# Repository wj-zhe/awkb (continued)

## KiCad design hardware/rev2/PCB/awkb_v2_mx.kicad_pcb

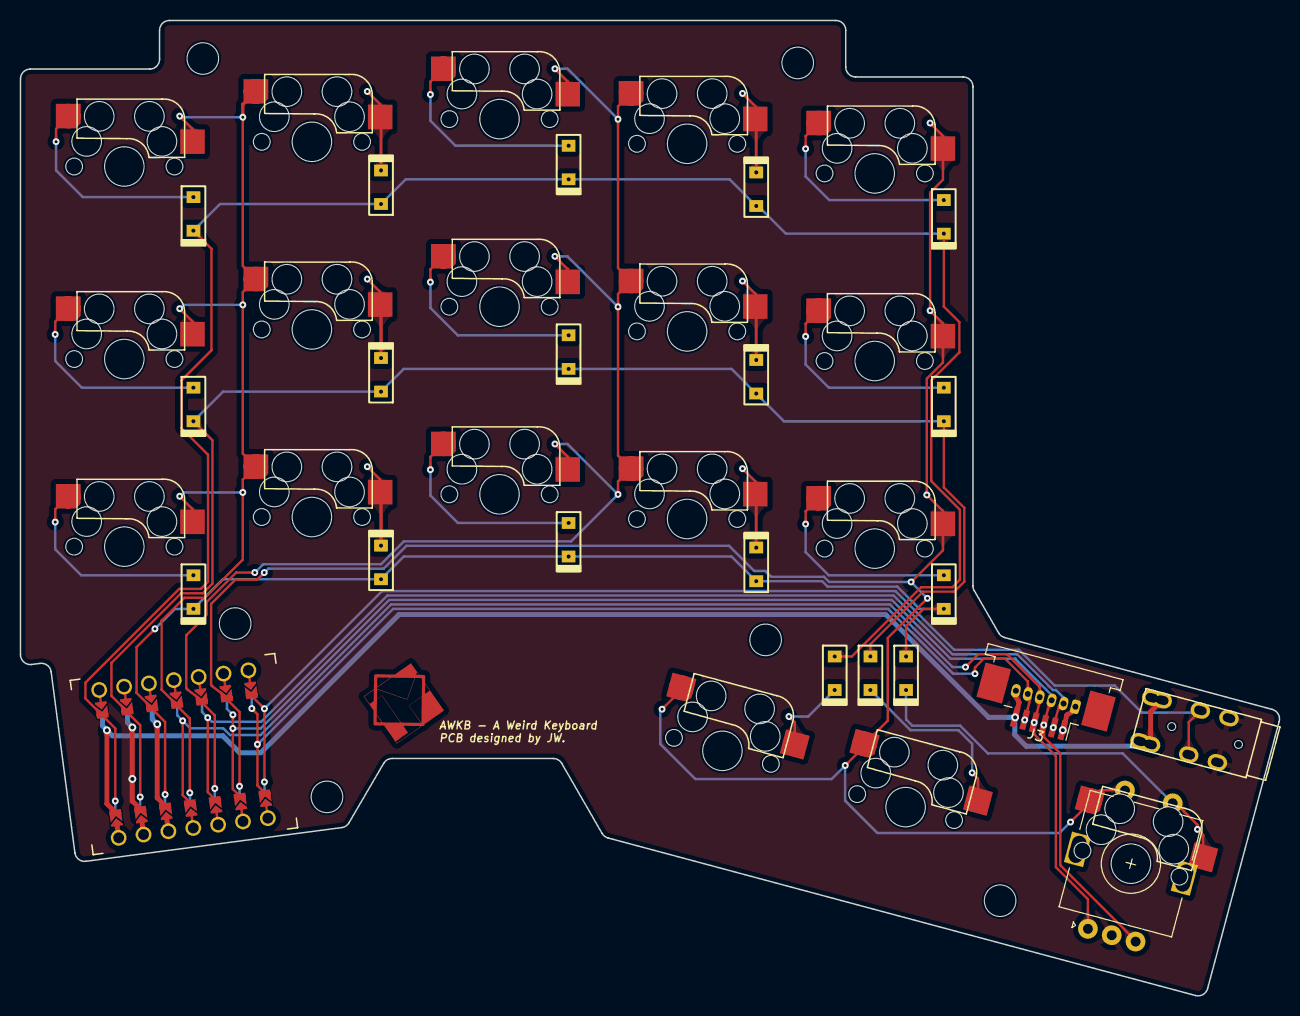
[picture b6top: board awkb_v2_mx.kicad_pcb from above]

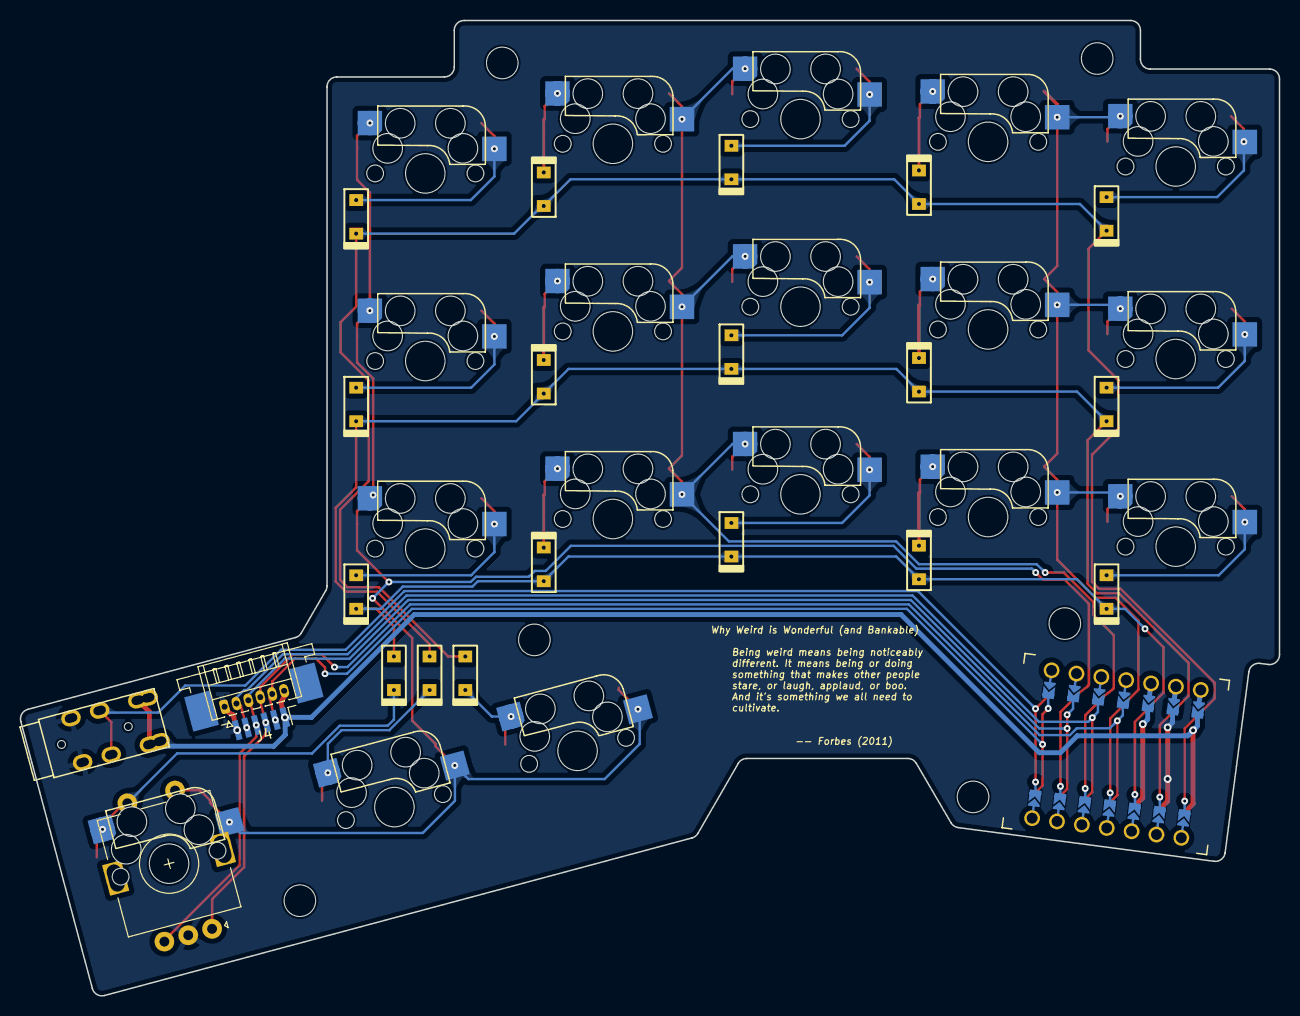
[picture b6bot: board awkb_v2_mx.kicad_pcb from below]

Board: 2 copper layers, 127.5 x 98.8 mm, 48 parts (3 on the bottom side), 31 nets.

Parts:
D1, D2, D3, D4, D5, D6, D7, D8, D9, D10, D11, D12, D13, D14, D15, D16, D17, D18: Diode; Diode_SOD123_THT_2
EC1: Rotary_Encoder_Switch; RotaryEncoder_Alps_EC11E-Switch_Vertical_H20mm
J1: 4PIN; TRRS-PJ-DPB2_mod
J2: Conn_01x06_Female; Hirose_DF13-06P-1.25DS_1x06_P1.25mm_Horizontal
J3, J4: Conn_01x06_Female; TE_84952-6_1x06-1MP_P1.0mm_Horizontal
SW1: SW1; CherryMX_Hotswap
SW2: SW2; CherryMX_Hotswap
SW3: SW3; CherryMX_Hotswap
SW4: SW4; CherryMX_Hotswap
SW5: SW5; CherryMX_Hotswap
SW6: SW6; CherryMX_Hotswap
SW7: SW7; CherryMX_Hotswap
SW8: SW8; CherryMX_Hotswap
SW9: SW9; CherryMX_Hotswap
SW10: SW10; CherryMX_Hotswap
SW11: SW11; CherryMX_Hotswap
SW12: SW12; CherryMX_Hotswap
SW13: SW13; CherryMX_Hotswap
SW14: SW14; CherryMX_Hotswap
SW15: SW15; CherryMX_Hotswap
SW16: SW16; CherryMX_Hotswap
SW17: SW17; CherryMX_Hotswap
SW18: SW18; CherryMX_Hotswap
TH1, TH2, TH3, TH4, TH5, TH6: HOLE; MountingHole_3.2mm_M3
U1: SeeeduinoXIAO; Xiao THT jumper pad_flipped

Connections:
DATA: J1.2, U1.7 (PB08_A6_D6_TX)
GND: EC1.C, J1.3, J2.1, J3.1, J4.6, U1.13 (GND)
MISO: J2.2, J3.2, J4.5, U1.10 (PA5_A9_D9_MISO)
MOSI_ENCA: EC1.A, J2.4, J3.4, J4.3, U1.11 (PA6_A10_D10_MOSI)
NCS: J2.5, J3.5, J4.2, U1.8 (PB09_A7_D7_RX)
unnamed: D1.2 (A), SW1.1
unnamed: D2.1 (K), SW2.2
unnamed: D3.2 (A), SW3.1
unnamed: D4.1 (K), SW4.2
unnamed: D5.2 (A), SW5.1
unnamed: D6.2 (A), SW6.1
unnamed: D7.1 (K), SW7.2
unnamed: D8.2 (A), SW8.1
unnamed: D9.1 (K), SW9.2
unnamed: D10.2 (A), SW10.1
unnamed: D11.2 (A), SW11.1
unnamed: D12.1 (K), SW12.2
unnamed: D13.2 (A), SW13.1
unnamed: D14.1 (K), SW14.2
unnamed: D15.2 (A), SW15.1
unnamed: D16.1 (K), SW16.2
unnamed: D17.1 (K), SW17.2
SCLK_ENCB: EC1.B, J2.3, J3.3, J4.4, U1.9 (PA7_A8_D8_SCK)
VDD_5V: J1.1, J1.4, J2.6, J3.6, J4.1, U1.14 (5V)
col0: SW1.2, SW2.1, SW6.2, SW7.1, SW11.2, SW12.1, U1.4 (PA11_A3_D3)
col1: SW3.2, SW4.1, SW8.2, SW9.1, SW13.2, SW14.1, U1.5 (PA8_A4_D4_SDA)
col2: EC1.S2, SW5.2, SW10.2, SW15.2, SW16.1, SW17.1, SW18.1, U1.6 (PA9_A5_D5_SCL)
row0: D1.1 (K), D2.2 (A), D3.1 (K), D4.2 (A), D5.1 (K), D16.2 (A), U1.1 (PA02_A0_D0)
row1: D6.1 (K), D7.2 (A), D8.1 (K), D9.2 (A), D10.1 (K), D17.2 (A), U1.2 (PA4_A1_D1)
row2: D11.1 (K), D12.2 (A), D13.1 (K), D14.2 (A), D15.1 (K), D18.2 (A), U1.3 (PA10_A2_D2)
sw_row: D18.1 (K), EC1.S1, SW18.2

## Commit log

2023-06-22 Added firmware to repository
2023-06-22 fixes applied
2023-06-22 USART half-duplex fix
2023-07-02 Major changes.
2023-07-30 Added media control on Layer 2, etc
2023-11-20 Updated firmware.
2024-02-12 Re-organized rev1 hardware files.
2024-02-12 Added rev2 hardware files.
2024-02-12 Updated firmware directory.
2024-02-12 Added .gitignore
2024-02-12 Removed ._firmware
2024-02-12 Re-uploaded firmware directory.
2024-02-12 Added README.md and related images.
2024-06-04 Updated firmware for rev2
2024-07-21 Made some changes.
2024-08-05 Grouped rev1/2 into '/split' directory
2024-08-05 Pre-alpha stage: Making monosplit.
2024-08-06 Grouped rev1 and rev2 into split directory
2024-08-06 Added firmware for monosplit without test as the hardware was not built
2024-08-26 Non-essential change in firmware; Modified monosplit hardward
2024-09-02 Re-organized hardware directory.. again
2024-09-12 Renamed files in 36 split and 34 split variants
2024-09-12 First production (with case) commit
2024-09-15 Reorganized firmware directory into 34_monosplit, 34_split and 36_split with partially common keymaps
2024-09-17 Updated for 34 split variant with right side as master
2024-09-22 Reorganized firmware directory in order to use common scripts and easies maintenance
2024-09-22 Minor changes on case design
2024-09-25 Multiple changes to firmware
2024-10-03 Separated keymap setting for 34_split and 34_monosplit. Some other changes.
2024-10-03 Added file wrongfully not included in previous commit
2024-10-07 Currently settled to this firmware revision with some cirque trackpad control in a separate file. Consider auto-mouse-layer replaced with custom code in next revision.
2024-10-19 Updated cirque trackpad contour line and alignment notches
2024-10-23 Added host-os-based customs keycodes. Keymap and combos updates. Other changes.
2024-10-25 Addes manual OS switch; updated auto_mouse control more granual; keymap updates
2024-10-30 Updated keymaps here and there.
2024-10-30 Made case for 23mm and 35mm cirque trackpad compatetive variants, accordingly
2024-11-03 Custom scroll on cirque with greater movement divisor and cap on h/v movements. Other tweaks to keymap.c, etc.
2024-11-10 Added auto-mouse layer configuration, relative changes to rgblight.c and other changes.
2024-11-10 Moved layer related functions to 34_monosplit specific folder; other changes.
2024-12-14 MAJOR CHANGE: Favoured keymaps in separate and indipendant directories instead of sourcing from common in previous commit
2025-05-30 Splited 34 monosplit into two projects of 34 and 36 keys, respectively
2025-05-30 Unfinished upgrade on 36 split version
2025-10-17 Modified firmware to add AUTO_MOUSE_LAYER
2025-10-17 Removed mouse button keys on several layers
2026-03-11 First upload of v3
    Production ready main and peripheral hardware and firmware
2026-03-14 Reorganized directory completely
2026-04-06 rev3: added fsr base line automatic setting mechanism
2026-04-25 36 rev3: properly functional firmware
